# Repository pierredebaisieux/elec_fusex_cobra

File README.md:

# elec_fusex_cobra
électronique et télémétrie embarquées dans la fusée expérimentale Cobra de l'association LéoFly

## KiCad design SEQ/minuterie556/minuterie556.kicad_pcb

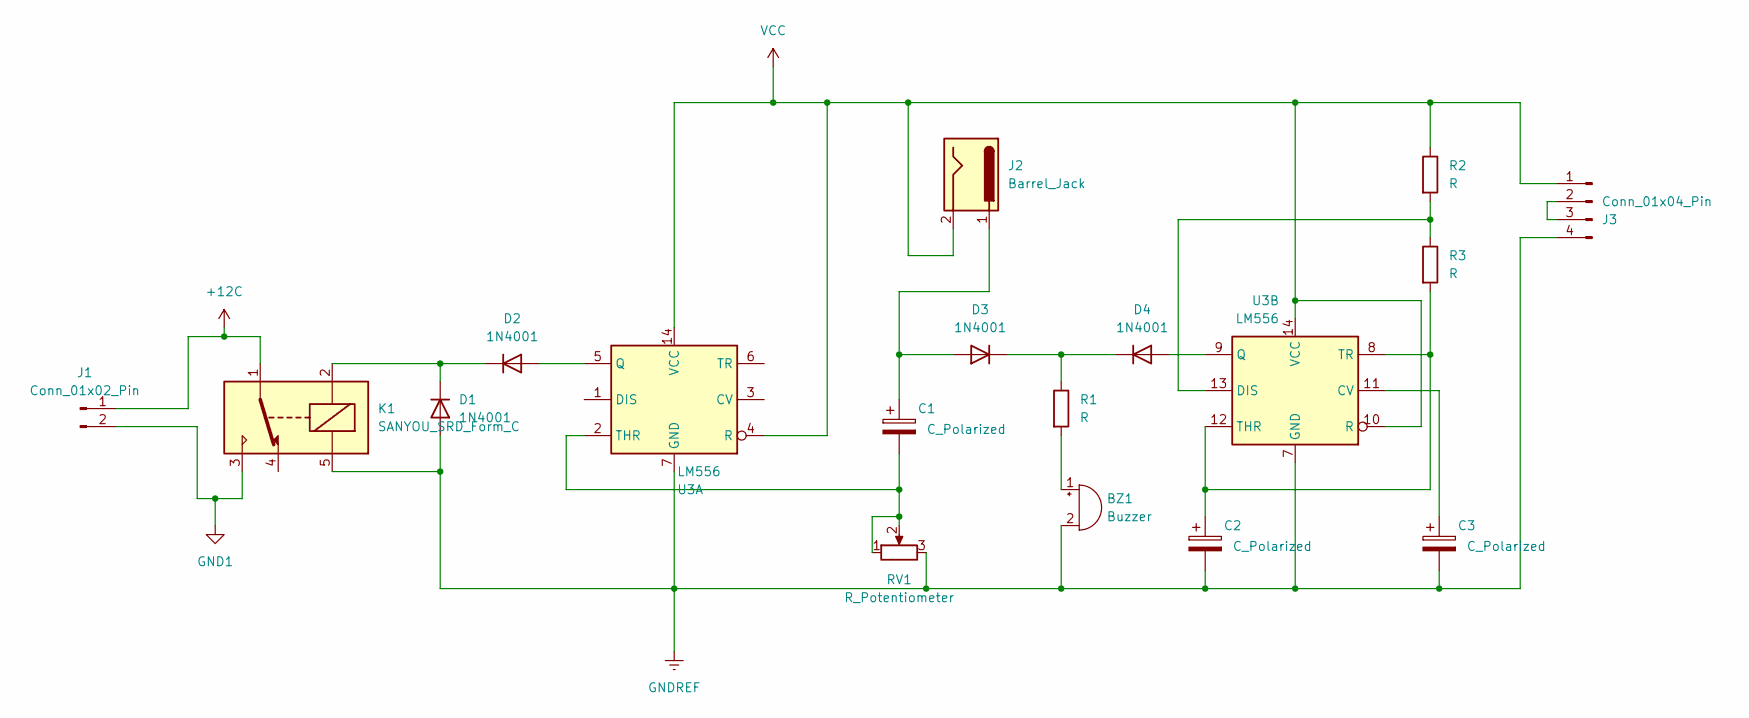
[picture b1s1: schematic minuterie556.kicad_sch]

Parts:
BZ1: Buzzer; Buzzer_12x9.5RM7.6
C1: C_Polarized; CP_Radial_D8.0mm_P2.50mm
C2, C3: C_Polarized; CP_Radial_D5.0mm_P2.50mm
D1, D2, D3, D4: 1N4001; D_DO-41_SOD81_P7.62mm_Horizontal
J1: Conn_01x02_Pin; JST_EH_B2B-EH-A_1x02_P2.50mm_Vertical
J2: Barrel_Jack; JST_EH_B2B-EH-A_1x02_P2.50mm_Vertical
J3: Conn_01x04_Pin; JST_EH_B4B-EH-A_1x04_P2.50mm_Vertical
K1: SANYOU_SRD_Form_C; Relay_SPDT_SANYOU_SRD_Series_Form_C
R1, R2, R3: R; R_Axial_DIN0207_L6.3mm_D2.5mm_P10.16mm_Horizontal
RV1: R_Potentiometer; Potentiometer_Bourns_3296W_Vertical
U3: LM556; DIP-14_W7.62mm

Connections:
+12C: J1.1, K1.1
GND1: J1.2, K1.3
GNDREF: BZ1.2 (+), C2.2, C3.2, D1.2 (A), J3.4, K1.5, RV1.3, U3.7 (GND)
unnamed: BZ1.1 (-), R1.2
unnamed: D1.1 (K), D2.1 (K), K1.2
unnamed: D2.2 (A), U3.5 (Q)
unnamed: C1.1, D3.2 (A), J2.1
unnamed: D3.1 (K), D4.1 (K), R1.1
unnamed: D4.2 (A), U3.9 (Q)
unnamed: J3.2, J3.3
unnamed: C1.2, RV1.1, RV1.2, U3.2 (THR)
unnamed: C3.1, U3.11 (CV)
unnamed: R2.2, R3.1, U3.13 (DIS)
unnamed: C2.1, R3.2, U3.8 (TR), U3.12 (THR)
VCC: J2.2, J3.1, R2.1, U3.4 (R), U3.10 (R), U3.14 (VCC)

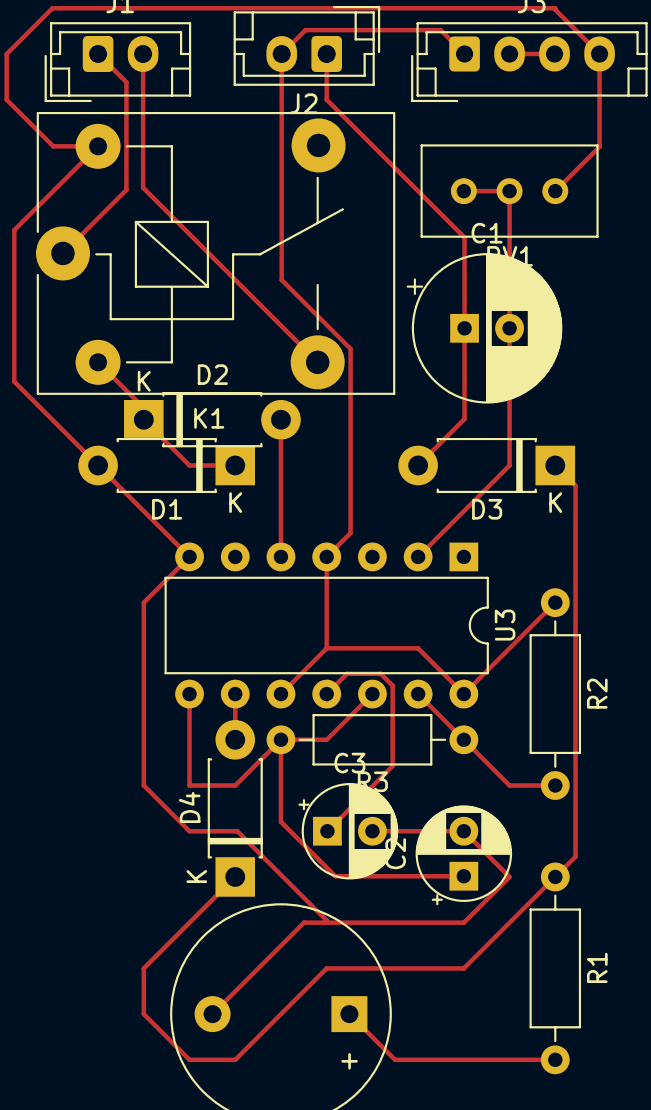
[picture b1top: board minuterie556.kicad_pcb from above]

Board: 2 copper layers, 17 parts (0 on the bottom side), 15 nets.

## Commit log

2023-11-19 changement read me
2023-11-19 recuperation travaux minuterie double 555
2023-11-19 recuperation travaux minuterie 556
2023-11-19 disposition en rectangle
2023-12-26 TX creation
